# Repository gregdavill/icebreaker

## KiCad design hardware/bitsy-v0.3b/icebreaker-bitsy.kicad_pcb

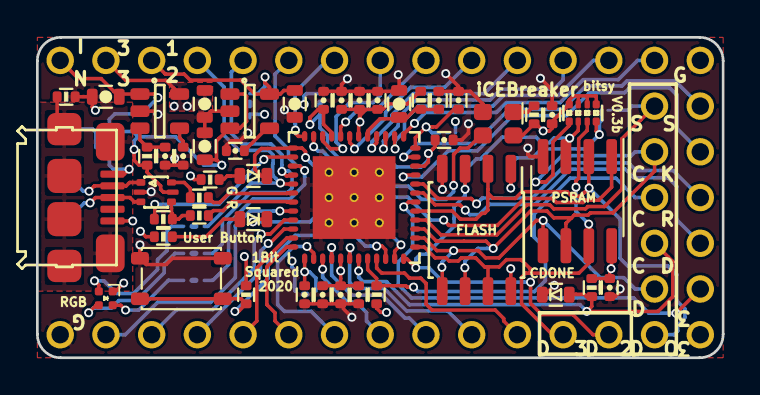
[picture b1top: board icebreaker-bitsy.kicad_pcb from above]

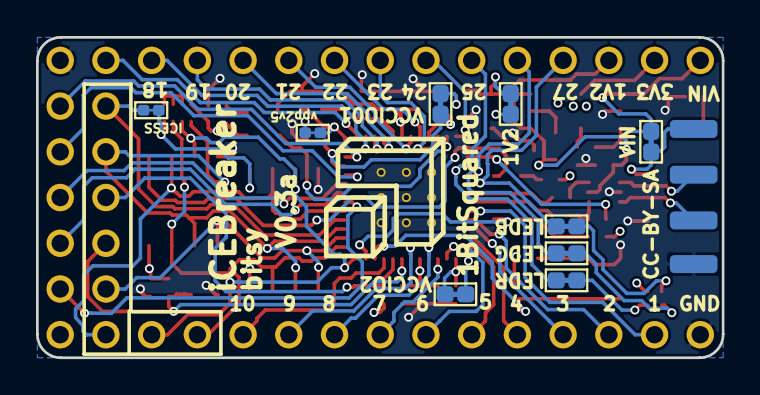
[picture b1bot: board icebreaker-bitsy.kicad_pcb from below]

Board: 4 copper layers, 38.1 x 17.8 mm, 100 parts (13 on the bottom side), 66 nets.

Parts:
C2, C5, C8, C15: 4u7; C_0603
C3, C11, C28, C38: 10n; C_0402
C4, C22, C25, C26, C27, C30, C31, C37: 100n; C_0402
C23, C36, C39: 1u; C_0402
C24: 10u; C_0603
C35: DNP; C_0402
D1: FC-B1010RGBT-HG; LED_TRI_1010
D3: BLU; D_0603
D4: GRN; D_0603
D5: RED; D_0603
J1, J2, J3, J4, J5, J6, J7, J8, J9, J10, J11, J12, J13, J20, J21, J22, J23, J24, J25, J26, J27, J28, J29, J30, J31, J32, J33, J34, J35, J36, J37, J41, J42, J43, J44, J45, J46, J47, J48, J49: Conn_01x01; Pin_Header_Straight_Round_1x01
J14, J15, J16, J17, J19, J38, J39: Jumper; J_NC_0603_30
J18, J40: Jumper; J_NC_0402_15
P1: USB_OTG; Connector_USB_Micro_B_SMD
P2, P3, P4, P5: UP; PAD_SMD_1x2.65
R1: 1M; R_0402
R2: 1k5; R_0402
R3, R7, R13, R19: 10k; R_0402
R4, R6: 22E; R_0402
R10: 100E; R_0402
R11: 10k; R_Array_Convex_4x0402
R12: 2k2; R_0402
R14, R15: 330E; R_0402
SW1: TACT; SW_SPST_3x4x2.5
U1: USBLC6-2; SOT-666
U2: 3.3V; SOT-23-5
U3: 1V2; SOT-23-5
U4: LY68L6400; SOIC-8_3.9x4.9mm_P1.27mm
U5: W25Q; SOIC-8_5.3x5.3mm_Pitch1.27mm
U6: ICE5LP4K-SG48; QFN-48-1EP_7x7mm_Pitch0.5mm
X1: DSC6101CI1A-012.0000T; Oscillator_SMD_SCTF_S2DXX-4Pin_2.5x2.0mm

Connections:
+1V2: C15.1, J3.1, J14.2, U3.5
+3V3: C4.1, C5.1, C22.1, D1.1, J1.1, J2.1, J17.2, J19.2, J40.1, R7.1, R11.1, R11.3, R11.5, R11.7, R12.1, R13.2, R14.2, R15.2, R19.1, U2.5, U4.8, U5.8, X1.4
+5V: C2.1, C8.1, J4.1, J38.2, R3.1, U1.5, U2.1, U3.1, U3.3
/CLK: U6.35, X1.3
/FLASH_MISO-IO1: J24.1, U4.2, U5.2, U6.17
/FLASH_MOSI-IO0: J23.1, U4.5, U5.5, U6.14
/FLASH_SS: J18.1, R11.2, U5.1
/FLASH_~HLD~-~RST~-IO3: J26.1, R11.4, U4.7, U5.7, U6.13
/FLASH_~WP~-IO2: J25.1, R11.6, U4.3, U5.3, U6.12
/ICEVCC: C23.1, C25.1, C28.1, C36.1, C37.1, C38.1, J14.1, R10.2, U6.5, U6.30
/IOB_0A: J7.1, U6.46
/IOB_2A: J8.1, U6.47
/IOB_3B_G6: J9.1, U6.44
/IOB_4A: J10.1, U6.48
/IOB_5B: J11.1, U6.45
/IOB_6A: J12.1, U6.2
/IOB_8A: J13.1, U6.4
/IOB_9B: J20.1, U6.3
/IOB_13B: J44.1, U6.6
/IOB_16A: J45.1, U6.9
/IOB_23B: J49.1, U6.21
/IOB_25B_G3: J46.1, U6.20
/IOB_29B: J47.1, U6.19
/IOB_31B: J48.1, U6.18
/IOT_36B: J29.1, U6.25
/IOT_37A: J30.1, U6.23
/IOT_38B: J31.1, U6.27
/IOT_39A: J32.1, U6.26
/IOT_41A: J33.1, U6.28
/IOT_42B: J34.1, U6.31
/IOT_43A: J35.1, U6.32
/IOT_44B: J36.1, U6.34
/IOT_48B: J37.1, U6.36
/USB_DET: R2.1, U6.38
/USB_N: R4.1, U6.42
/USB_P: R6.1, U6.43
/UVBUS: J38.1, P1.1, P2.1
/VCCIO_01: C30.1, C31.1, J19.1, U6.22, U6.33
/VCCIO_2: C27.2, J17.1, U6.1
/iCE_CDONE: D3.A, J27.1, R12.2, U6.7
/iCE_CRESET: J28.1, R19.2, U6.8
/iCE_SCK: J22.1, R11.8, U4.6, U5.6, U6.15
/iCE_SS_B: J18.2, J21.1, U6.16
/iUD+: R2.2, R6.2, U1.4
/iUD-: R4.2, U1.6
/shield: P1.GND, R1.2
/xUD+: P1.3, P4.1, U1.3
/xUD-: P1.2, P3.1, U1.1
/~BUTTON: R13.1, SW1.1, U6.10
/~LEDG: D4.C, U4.1, U6.37
/~LEDR: D5.C, U6.11
/~LED_BLU: J15.1, J43.1, U6.41
/~LED_GRN: J16.1, J42.1, U6.40
/~LED_RED: J39.1, J41.1, U6.39
GND: C2.2, C3.2, C4.2, C5.2, C8.2, C11.2, C15.2, C22.2, C23.2, C24.2, C25.2, C26.2, C27.1, C28.2, C30.2, C31.2, C35.2, C36.2, C37.2, C38.2, C39.2, D3.C, J5.1, J6.1, P1.5, P5.1, R1.1, SW1.2, U1.2, U2.2, U3.2, U4.4, U5.4, U6.49, X1.2
unnamed: C3.1, U2.4
unnamed: C11.1, U3.4
unnamed: C24.1, C26.1, R10.1, U6.29
unnamed: C35.1, J40.2, U6.24
unnamed: C39.1, R3.2, U2.3
unnamed: D1.2, J39.2
unnamed: D1.3, J16.2
unnamed: D1.4, J15.2
unnamed: D4.A, R14.1
unnamed: D5.A, R15.1
unnamed: R7.2, X1.1

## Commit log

2020-04-05 Minor cleanups, finishing up for prototype order.
    This is the status from the ad hoc stream from Apr 4th 2020.
2020-04-05 Quick route of single sided variant
2020-04-05 Clean up routing

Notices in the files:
hardware/bitsy-v0.3b/icebreaker-bitsy.kicad_pcb:
(C) 2018-2020 Piotr Esden-Tempski
(C) 2018-2020 1BitSquared
License: CC-BY-SA 4.0
CC-BY-SA
